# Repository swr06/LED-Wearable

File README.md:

# LED-Wearable
LED Wearable that displays patterns, based on ATTiny1614

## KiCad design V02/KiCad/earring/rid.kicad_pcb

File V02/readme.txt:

This version isnt entirely independent. It uses a premade 4x4 led matrix (WS2812B 4x4) and interfaces that instead. Custom footprint used. 

https://www.amazon.in/HEAVENGLOW-Full-Color-Individual-Electrical-Industrial/dp/B0GLXNSCTH

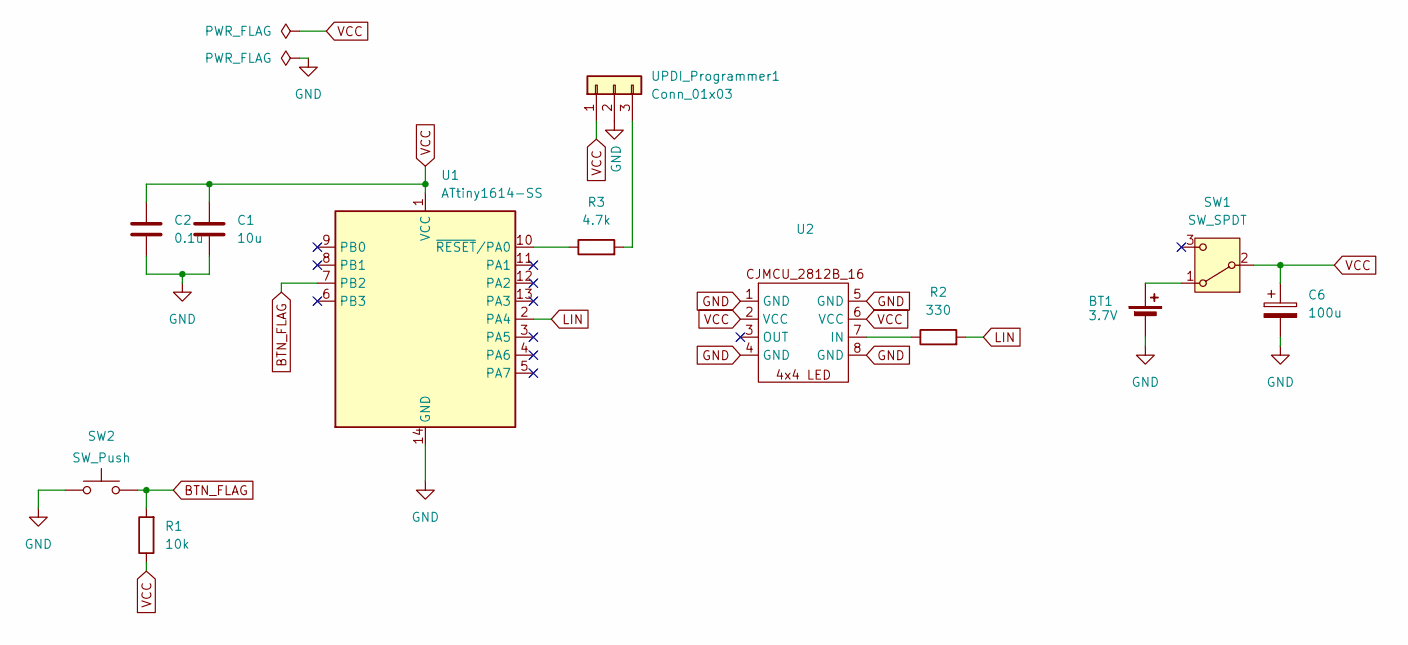
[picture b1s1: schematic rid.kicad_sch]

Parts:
BT1: 3.7V; PinHeader_1x02_P2.54mm_Vertical
C1: 10u; C_1206_3216Metric
C2: 0.1u; C_1206_3216Metric
C6: 100u; CP_Elec_5x5.3
R1: 10k; R_1206_3216Metric
R2: 330; R_1206_3216Metric
R3: 4.7k; R_1206_3216Metric
SW1: SW_SPDT; SW_SPDT_Shouhan_MSK12C02
SW2: SW_Push; SW_Push_1P1T_NO_E-Switch_TL3301NxxxxxG
U1: ATtiny1614-SS; SOIC-14_3.9x8.7mm_P1.27mm
U2: CJMCU_2812B_16_30x30
UPDI_Programmer1: Conn_01x03; PinHeader_1x03_P2.54mm_Vertical

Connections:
BTN_FLAG: R1.2, SW2.2, U1.7 (PB2)
GND: BT1.2 (-), C1.2, C2.2, C6.2, SW2.1, U1.14 (GND), U2.1 (GND), U2.4 (GND), U2.5 (GND), U2.8 (GND), UPDI_Programmer1.2
LIN: R2.2, U1.2 (PA4)
unnamed: BT1.1 (+), SW1.1 (A)
unnamed: R3.1, U1.10 (~RESET/PA0)
unnamed: R2.1, U2.7 (IN)
unnamed: R3.2, UPDI_Programmer1.3
VCC: C1.1, C2.1, C6.1, R1.1, SW1.2 (B), U1.1 (VCC), U2.2 (VCC), U2.6 (VCC), UPDI_Programmer1.1

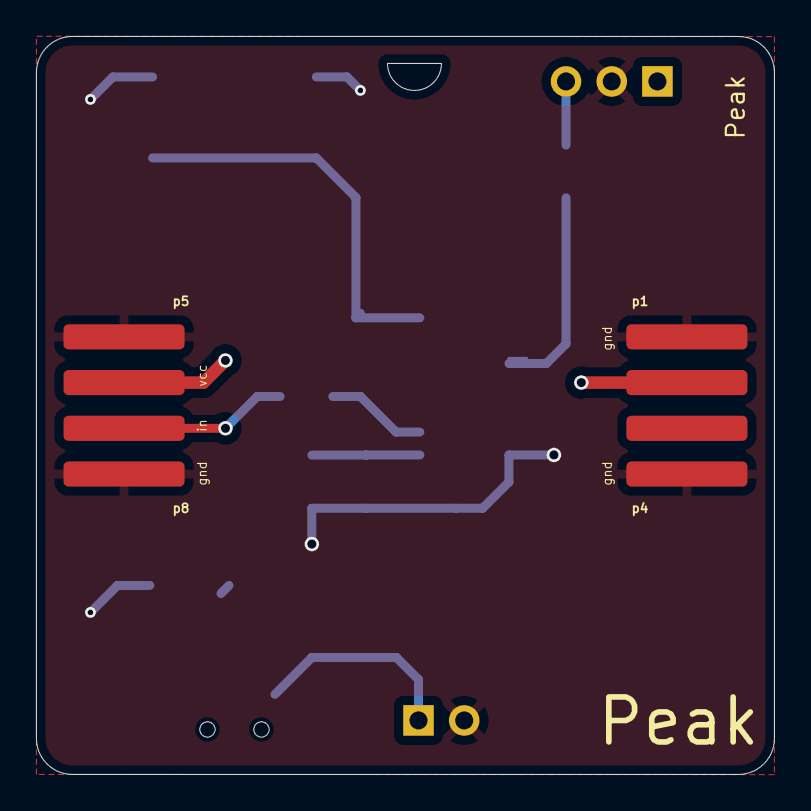
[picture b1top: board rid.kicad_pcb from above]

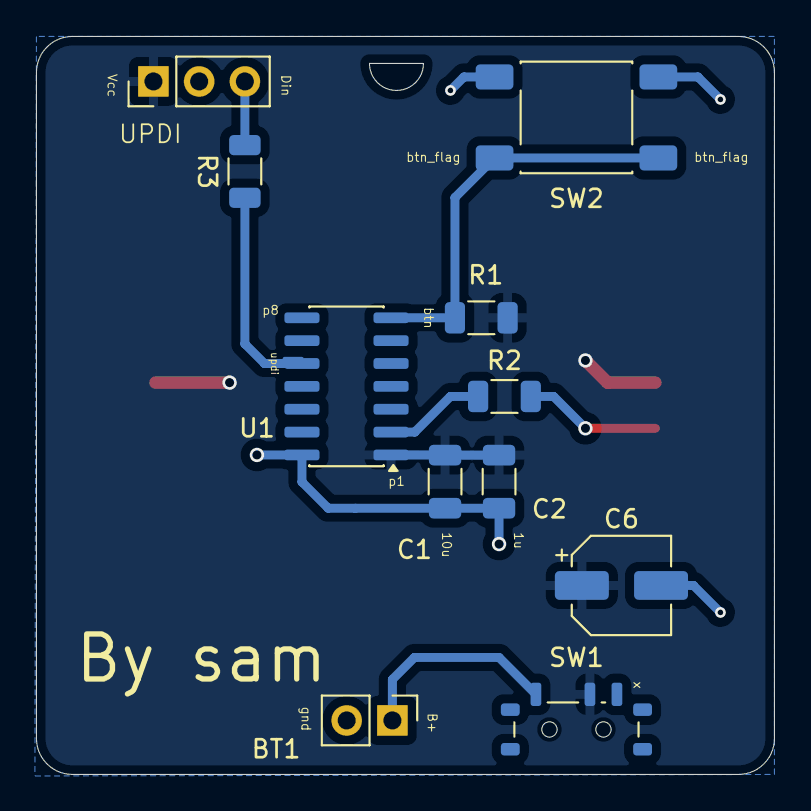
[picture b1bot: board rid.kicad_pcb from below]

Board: 2 copper layers, 41.0 x 41.0 mm, 12 parts (11 on the bottom side), 8 nets.

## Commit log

2026-05-13 yeee
